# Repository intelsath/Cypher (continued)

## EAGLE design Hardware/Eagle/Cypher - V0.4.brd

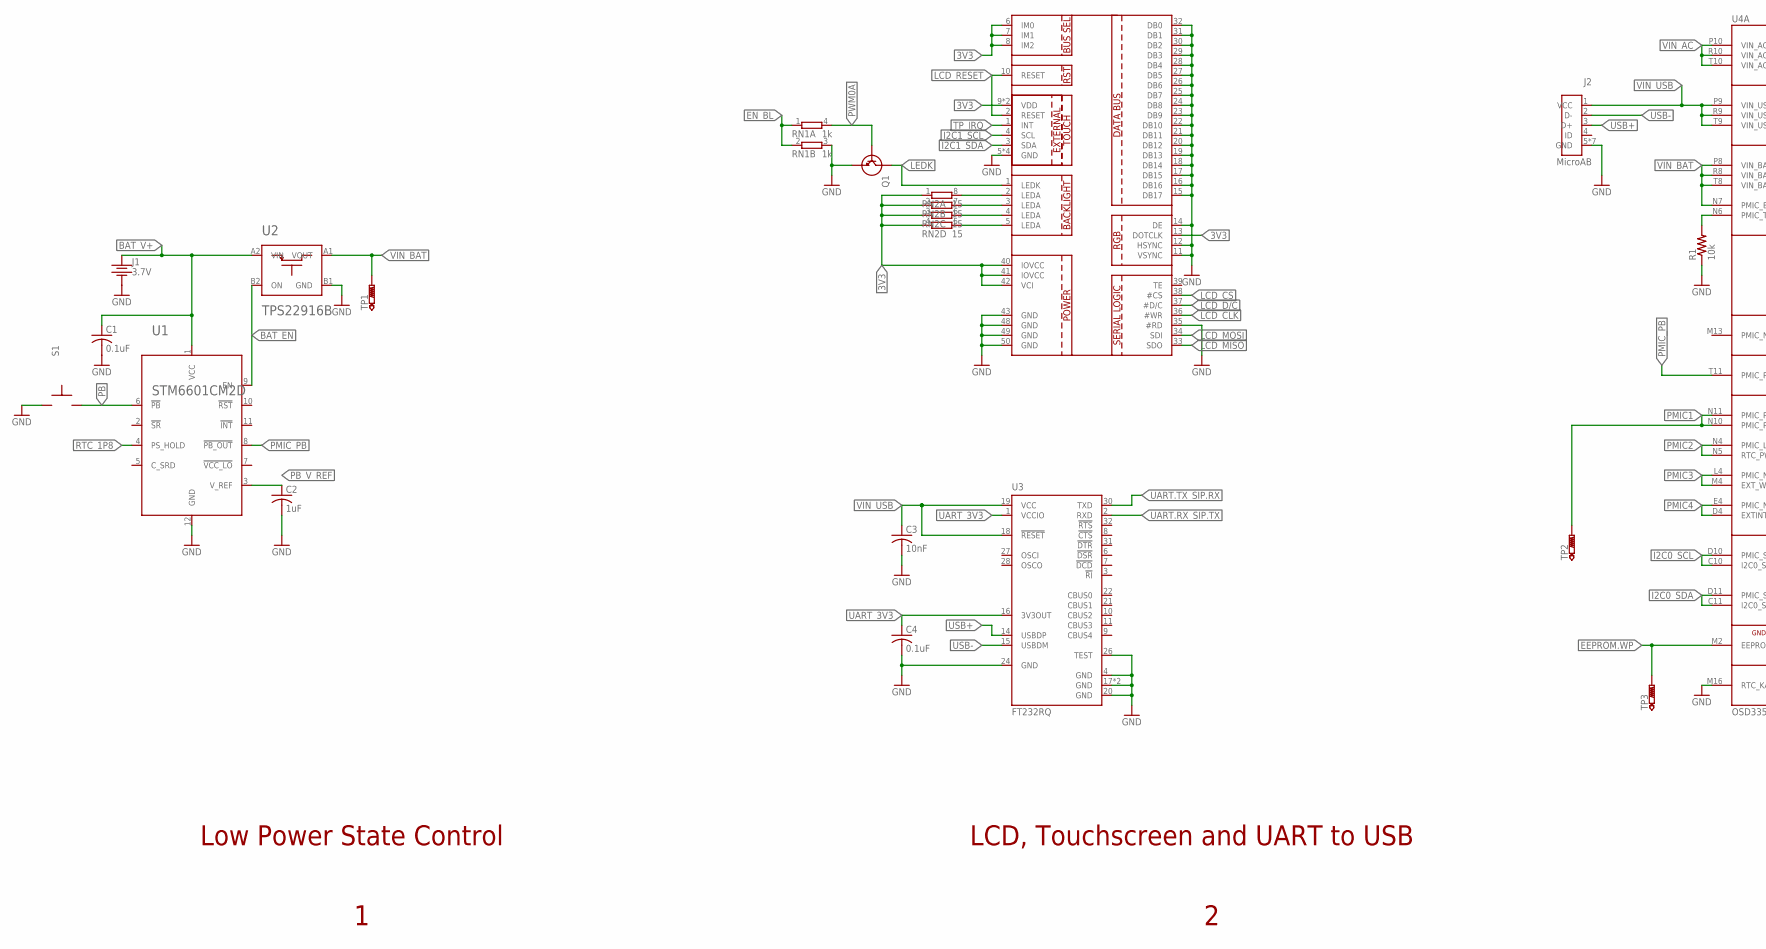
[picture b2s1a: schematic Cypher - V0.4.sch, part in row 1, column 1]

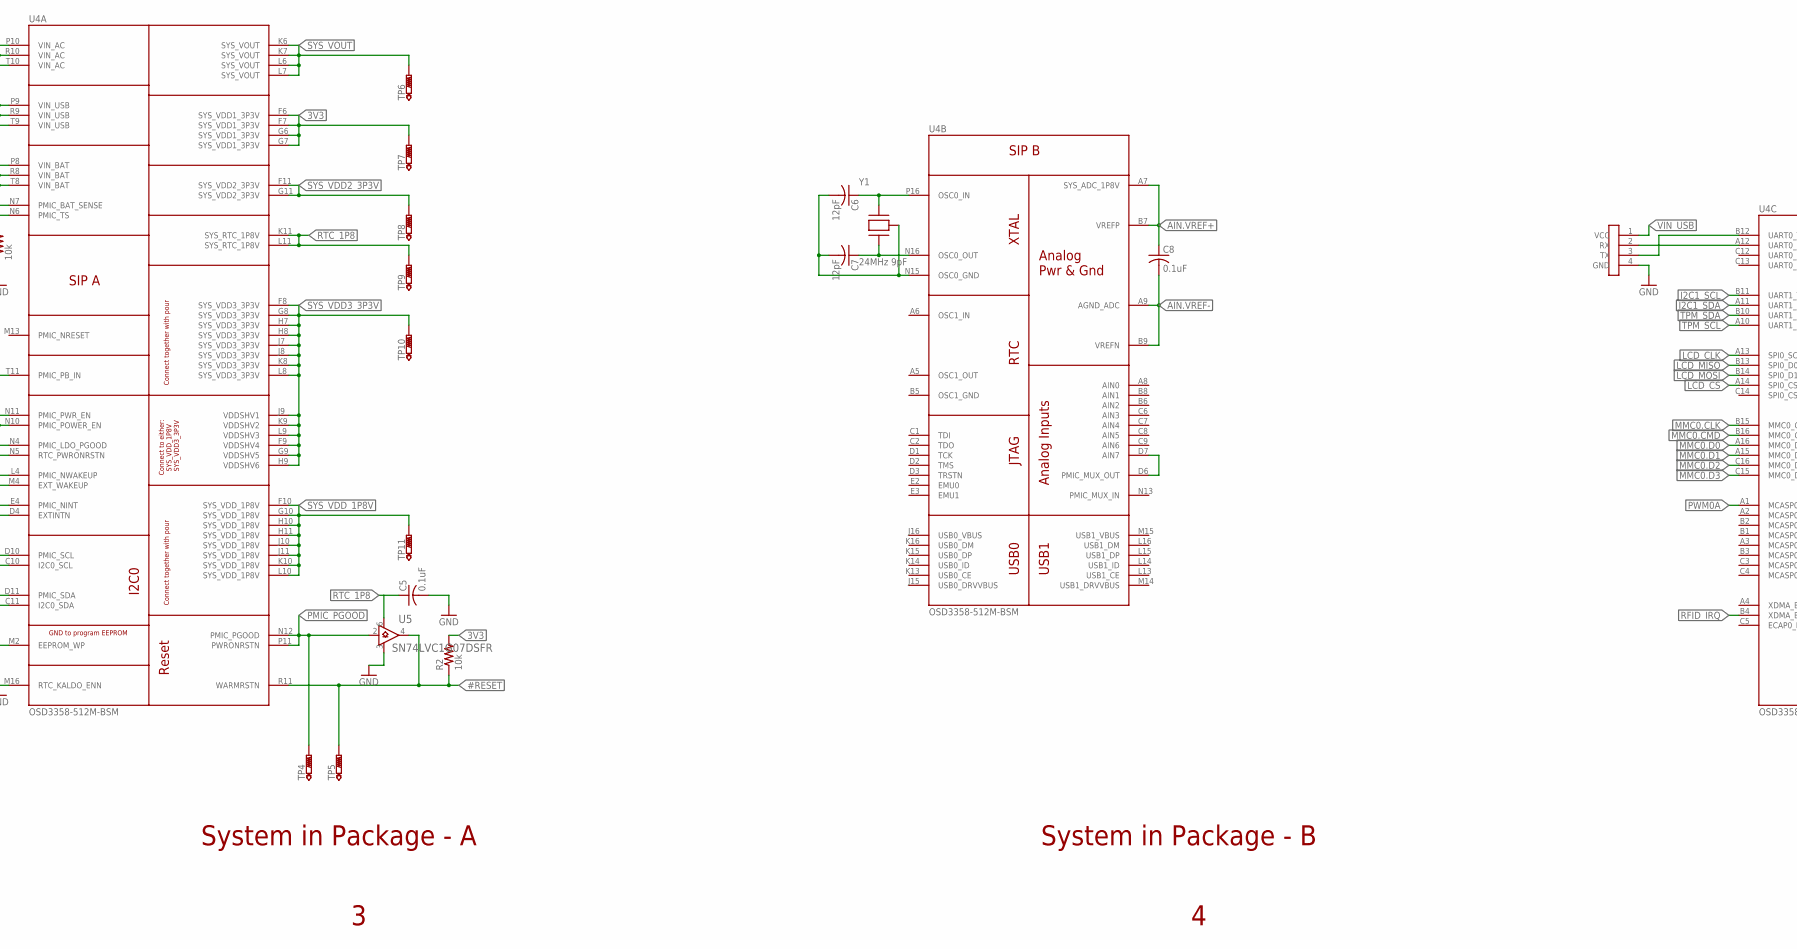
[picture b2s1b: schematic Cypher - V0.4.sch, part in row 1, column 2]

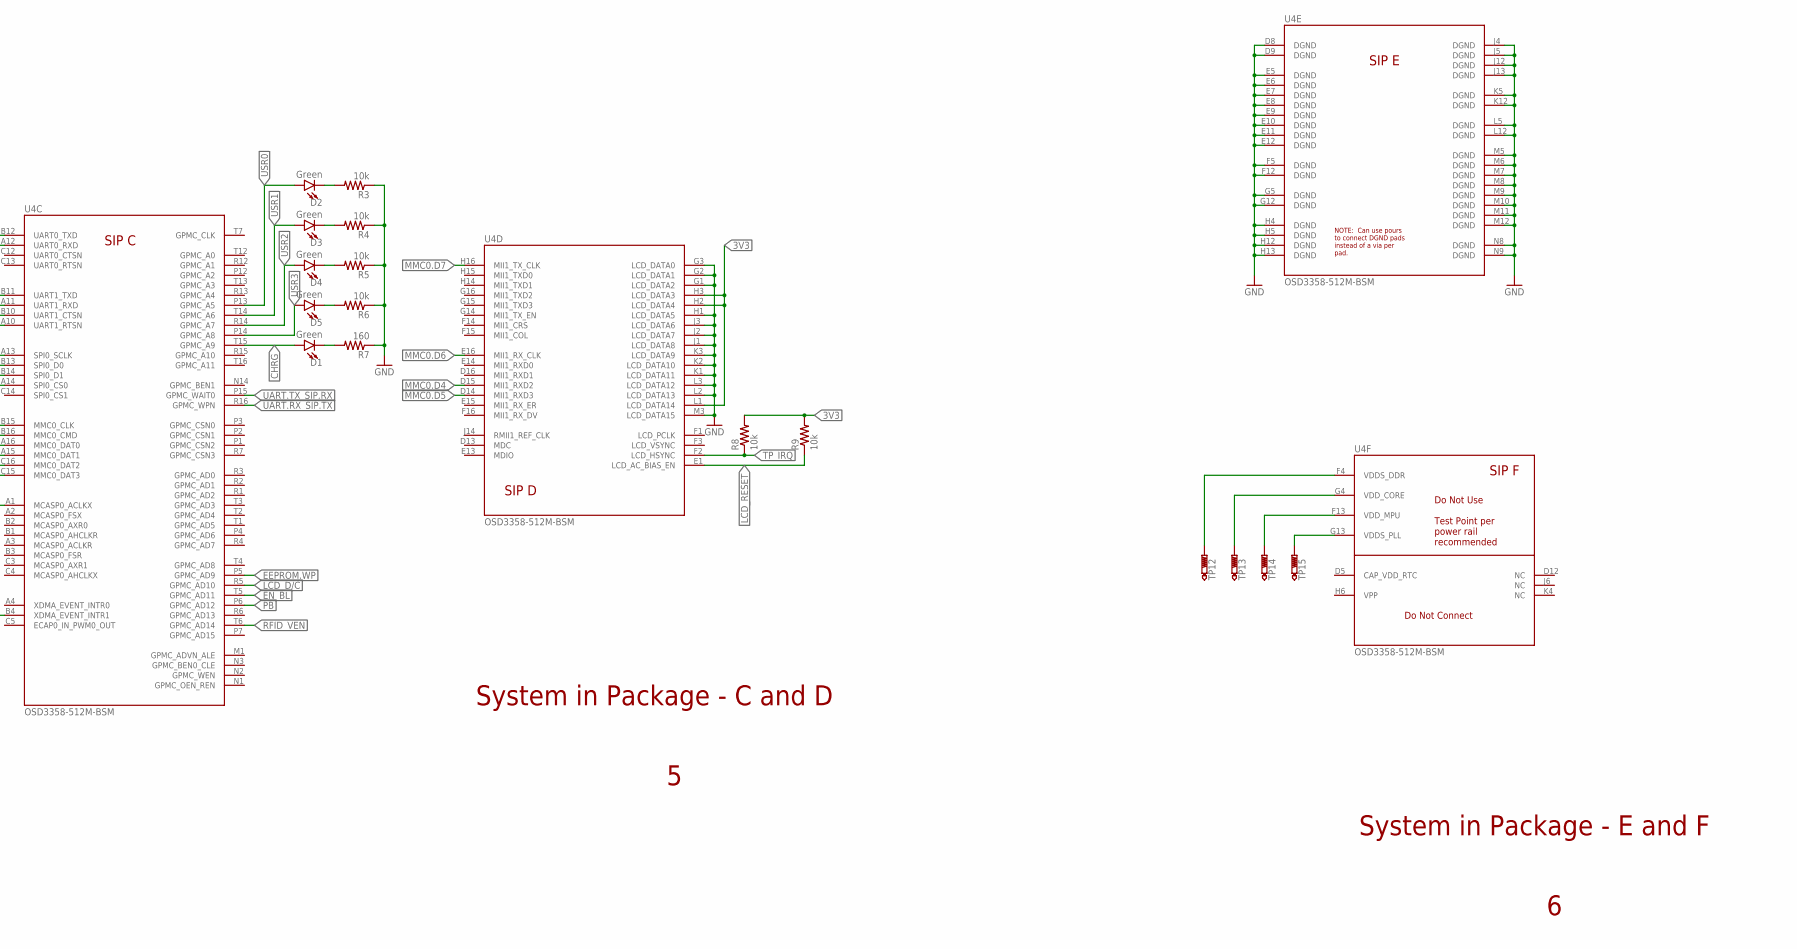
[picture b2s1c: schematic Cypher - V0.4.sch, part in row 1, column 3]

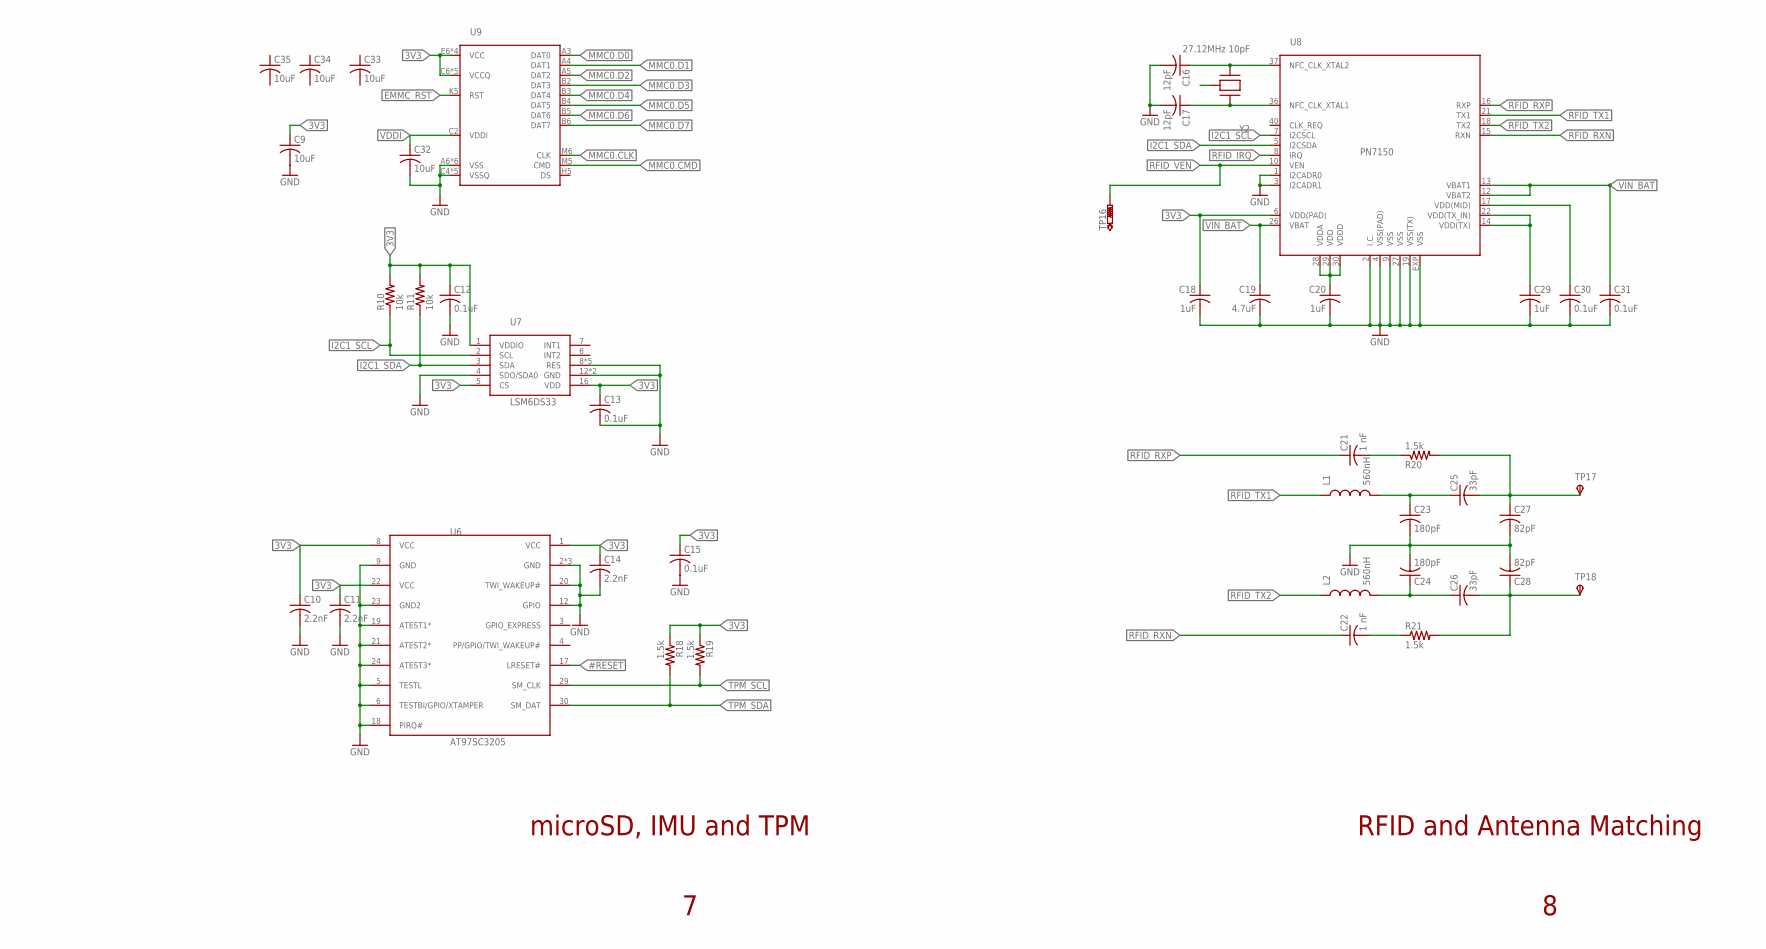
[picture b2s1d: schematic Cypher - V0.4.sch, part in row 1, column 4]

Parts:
C1, C4, C5, C8, C12, C13, C15, C30, C31: 0.1uF; C0402
C2, C18, C20, C29: 1uF; C0402
C3: 10nF; C0402
C6, C7, C16, C17: 12pF; C0402
C9, C32, C33, C34, C35: 10uF; C0402
C10, C11, C14: 2.2nF; C0402
C19: 4.7uF; C0402
C21, C22: 1 nF; C0603
C23, C24: 180pF; C0402
C25, C26: 33pF; C0402
C27, C28: 82pF; C0402
D1, D2, D3, D4, D5: Green; LED-0603
J1: 3.7V; SH_CONNECTOR
J2: MicroAB; MICRO-USB-AB-SMD
J3: UARTPINSSH; SM04B-SRSS-TB
L1, L2: 560nH; C0402
Q1: MMBT2222ASOT23; SOT-23-3
R1, R2, R3, R4, R5, R6, R8, R9, R10, R11: 10k; R0402
R7: 160; R0402
R18, R19, R20, R21: 1.5k; R0402
RN1: 1k; EXBV4V
RN2: 15; EXBN8V
S1: PUSHBUTTON1.2; EVQ-PUK
TP1, TP2, TP3, TP4, TP5, TP6, TP7, TP8, TP9, TP10, TP11, TP12, TP13, TP14, TP15, TP16: PTR1B1,27; B1,27
TP17, TP18: TPSB2,54; B2,54
U1: STM6601CM2D; TDFN12
U2: TPS22916B; WSON-4PIN
U3: FT232RQ; QFN32; MPN FT232RQ-REEL
U4: OSD3358-512M-BSM; OSD335X-BGA-256; MPN BB-POCKET
U5: SN74LVC1G07DSFR; SON35P100X100X40-6N
U6: AT97SC3205; QFN32-4MM
U7: LSM6DS33; LGA-16; MPN LSM6DS33TR
U8: PN7150; HVQFN40
U9: EMMC_EM-20; 153-LFBGA
XU1: CAPTOUCHSCREEN_6PINFPC10PIN; DF37NB-10DS-0.4V
XU2: ILI9388_50PIN_SOCKET; FPC/FFC_50PIN_0.5MMPITCH
Y1: 24MHz 9pF; 4-SMD
Y2: 27.12MHz 10pF; XRCGB

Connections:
3V3: C9.1, C10.1, C11.1, C12.1, C13.1, C14.1, C15.1, C18.1, R2.2, R8.2, R9.2, R10.2, R11.2, R18.1, R19.1, RN2.1, RN2.2 (1), RN2.3 (1), RN2.4 (1), TP7.TP, U4.F6 (SYS_VDD1_3P3V), U4.F7 (SYS_VDD1_3P3V), U4.G6 (SYS_VDD1_3P3V), U4.G7 (SYS_VDD1_3P3V), U4.H2 (LCD_DATA4), U4.H3 (LCD_DATA3), U4.L1 (LCD_DATA14), U6.1 (VCC), U6.8 (VCC), U6.22 (VCC), U7.1 (VDDIO), U7.5 (CS), U7.16 (VDD), U8.6 (VDD(PAD)), U9.C6 (VCCQ), U9.E6 (VCC), U9.F5 (VCC), U9.J10 (VCC), U9.K9 (VCC), U9.M4 (VCCQ), U9.N4 (VCCQ), U9.P3 (VCCQ), U9.P5 (VCCQ), XU1.9 (VDD), XU1.10 (VDD), XU2.6 (IM0), XU2.7 (IM1), XU2.8 (IM2), XU2.13 (DOTCLK), XU2.40 (IOVCC), XU2.41 (IOVCC), XU2.42 (VCI)
#RESET: R2.1, TP5.TP, U4.R11 (WARMRSTN), U5.4 (Y), U6.17 (LRESET#)
AIN.VREF+: C8.1, U4.A7 (SYS_ADC_1P8V), U4.B7 (VREFP)
AIN.VREF-: C8.2, U4.A9 (AGND_ADC), U4.B9 (VREFN)
ANT_1: C25.2, C27.1, R20.2, TP17.TP
ANT_2: C26.2, C28.1, R21.2, TP18.TP
BAT_EN: U1.9 (EN), U2.B2 (ON)
BAT_V+: C1.1, J1.2 (V+), U1.1 (VCC), U2.A2 (VIN)
CHRG: D1.A, U4.T15 (GPMC_A9)
D2_CAT: D2.C, R3.2
D2_CAT1: D1.C, R7.2
D3_CAT: D3.C, R4.2
D4_CAT: D4.C, R5.2
D5_CAT: D5.C, R6.2
EEPROM.WP: TP3.TP, U4.M2 (EEPROM_WP), U4.P5 (GPMC_AD9)
EMCF_ANTM1: C23.1, C25.1, L1.2
EMCF_ANTM2: C24.1, C26.1, L2.2
EMMC_RST: U9.K5 (RST)
EN_BL: RN1.1, RN1.2 (1), U4.T5 (GPMC_AD11)
GND: C1.2, C2.2, C3.2, C4.2, C5.2, C9.2, C10.2, C11.2, C12.2, C13.2, C14.2, C15.2, C16.2, C17.2, C18.2, C19.2, C20.2, C23.2, C24.2, C27.2, C28.2, C29.2, C30.2, C31.2, C32.2, J1.1 (V-), J2.5 (GND), J2.PAD1 (GND), J2.PAD2 (GND), J2.PAD3 (GND), J2.PAD4 (GND), J2.PAD5 (GND), J2.PAD6 (GND), J3.4 (GND), Q1.E, R1.1, R3.1, R4.1, R5.1, R6.1, R7.1, RN1.3 (2), S1.2, S1.4 (2), U1.12 (GND), U2.B1 (GND), U3.4 (GND), U3.17 (GND), U3.20 (GND), U3.24 (GND), U3.26 (TEST), U3.EXP (GND), U4.D8 (DGND), U4.D9 (DGND), U4.E5 (DGND), U4.E6 (DGND), U4.E7 (DGND), U4.E8 (DGND), U4.E9 (DGND), U4.E10 (DGND), U4.E11 (DGND), U4.E12 (DGND), U4.F5 (DGND), U4.F12 (DGND), U4.G1 (LCD_DATA2), U4.G2 (LCD_DATA1), U4.G3 (LCD_DATA0), U4.G5 (DGND), U4.G12 (DGND), U4.H1 (LCD_DATA5), U4.H4 (DGND), U4.H5 (DGND), U4.H12 (DGND), U4.H13 (DGND), U4.J1 (LCD_DATA8), U4.J2 (LCD_DATA7), U4.J3 (LCD_DATA6), U4.J4 (DGND), U4.J5 (DGND), U4.J12 (DGND), U4.J13 (DGND), U4.K1 (LCD_DATA11), U4.K2 (LCD_DATA10), U4.K3 (LCD_DATA9), U4.K5 (DGND), U4.K12 (DGND), U4.L2 (LCD_DATA13), U4.L3 (LCD_DATA12), U4.L5 (DGND), U4.L12 (DGND), U4.M3 (LCD_DATA15), U4.M5 (DGND), U4.M6 (DGND), U4.M7 (DGND), U4.M8 (DGND), U4.M9 (DGND), U4.M10 (DGND), U4.M11 (DGND), U4.M12 (DGND), U4.M16 (RTC_KALDO_ENN), U4.N8 (DGND), U4.N9 (DGND), U5.3 (GND), U6.2 (GND), U6.5 (TESTL), U6.6 (TESTBI/GPIO/XTAMPER), U6.9 (GND), U6.12 (GPIO), U6.18 (PIRQ#), U6.19 (ATEST1*), U6.20 (TWI_WAKEUP#), U6.21 (ATEST2*), U6.23 (GND2), U6.24 (ATEST3*), U6.32 (GND), U6.EXP (GND), U7.4 (SDO/SDA0), U7.8 (RES), U7.9 (RES), U7.10 (RES), U7.11 (RES), U7.12 (GND), U7.13 (GND), U7.15 (RES), U8.1 (I2CADR0), U8.2 (I.C.), U8.3 (I2CADR1), U8.4 (VSS(PAD)), U8.9 (VSS), U8.19 (VSS(TX)), U8.27 (VSS), U8.EXP (VSS), U9.A6 (VSS), U9.C4 (VSSQ), U9.E7 (VSS), U9.G5 (VSS), U9.H10 (VSS), U9.J5 (VSS), U9.K8 (VSS), U9.N2 (VSSQ), U9.N5 (VSSQ), U9.P4 (VSSQ), U9.P6 (VSSQ), XU1.5 (GND), XU1.6 (GND), XU1.7 (GND), XU1.8 (GND), XU2.11 (VSYNC), XU2.12 (HSYNC), XU2.14 (DE), XU2.15 (DB17), XU2.16 (DB16), XU2.17 (DB15), XU2.18 (DB14), XU2.19 (DB13), XU2.20 (DB12), XU2.21 (DB11), XU2.22 (DB10), XU2.23 (DB9), XU2.24 (DB8), XU2.25 (DB7), XU2.26 (DB6), XU2.27 (DB5), XU2.28 (DB4), XU2.29 (DB3), XU2.30 (DB2), XU2.31 (DB1), XU2.32 (DB0), XU2.35 (#RD), XU2.43 (GND), XU2.48 (GND), XU2.49 (GND), XU2.50 (GND)
I2C0_SCL: U4.C10 (I2C0_SCL), U4.D10 (PMIC_SCL)
I2C0_SDA: U4.C11 (I2C0_SDA), U4.D11 (PMIC_SDA)
I2C1_SCL: R10.1, U4.B11 (UART1_TXD), U7.2 (SCL), U8.7 (I2CSCL), XU1.4 (SCL)
I2C1_SDA: R11.1, U4.A11 (UART1_RXD), U7.3 (SDA), U8.5 (I2CSDA), XU1.3 (SDA)
LCD_CLK: U4.A13 (SPI0_SCLK), XU2.36 (#WR)
LCD_CS: U4.A14 (SPI0_CS0), XU2.38 (#CS)
LCD_D/C: U4.R5 (GPMC_AD10), XU2.37 (#D/C)
LCD_MISO: U4.B13 (SPI0_D0), XU2.33 (SDO)
LCD_MOSI: U4.B14 (SPI0_D1), XU2.34 (SDI)
LCD_RESET: R9.1, U4.E1 (LCD_AC_BIAS_EN), XU1.2 (RESET), XU2.10 (RESET)
LEDA@2: RN2.8 (2), XU2.2 (LEDA)
LEDA@3: RN2.7 (2), XU2.3 (LEDA)
LEDA@4: RN2.6 (2), XU2.4 (LEDA)
LEDA@5: RN2.5 (2), XU2.5 (LEDA)
LEDK: Q1.C, XU2.1 (LEDK)
MMC0.CLK: U4.B15 (MMC0_CLK), U9.M6 (CLK)
MMC0.CMD: U4.B16 (MMC0_CMD), U9.M5 (CMD)
MMC0.D0: U4.A16 (MMC0_DAT0), U9.A3 (DAT0)
MMC0.D1: U4.A15 (MMC0_DAT1), U9.A4 (DAT1)
MMC0.D2: U4.C16 (MMC0_DAT2), U9.A5 (DAT2)
MMC0.D3: U4.C15 (MMC0_DAT3), U9.B2 (DAT3)
MMC0.D4: U4.D15 (MII1_RXD2), U9.B3 (DAT4)
MMC0.D5: U4.D14 (MII1_RXD3), U9.B4 (DAT5)
MMC0.D6: U4.E16 (MII1_RX_CLK), U9.B5 (DAT6)
MMC0.D7: U4.H16 (MII1_TX_CLK), U9.B6 (DAT7)
NC: Y2.2 (GND), Y2.4 (GND)
OSC_GND: C6.2, C7.2, U4.N15 (OSC0_GND), Y1.2 (GND), Y1.4 (GND)
PB: S1.1, S1.3 (1), U1.6 (!PB), U4.P6 (GPMC_AD12)
PB_V_REF: C2.1, U1.3 (V_REF)
PMIC1: TP2.TP, U4.N10 (PMIC_POWER_EN), U4.N11 (PMIC_PWR_EN)
PMIC2: U4.N4 (PMIC_LDO_PGOOD), U4.N5 (RTC_PWRONRSTN)
PMIC3: U4.L4 (PMIC_NWAKEUP), U4.M4 (EXT_WAKEUP)
PMIC4: U4.D4 (EXTINTN), U4.E4 (PMIC_NINT)
PMIC_MUX: U4.D6 (PMIC_MUX_OUT), U4.D7 (AIN7)
PMIC_PB: U1.8 (!PB_OUT), U4.T11 (PMIC_PB_IN)
PMIC_PGOOD: TP4.TP, U4.N12 (PMIC_PGOOD), U4.P11 (PWRONRSTN), U5.2 (A)
PMIC_TS: R1.2, U4.N6 (PMIC_TS)
PWM0A: Q1.B, RN1.4 (2), U4.A1 (MCASP0_ACLKX)
RFID_IRQ: U4.B4 (XDMA_EVENT_INTR1), U8.8 (IRQ)
RFID_MISC_1: C21.2, R20.1
RFID_MISC_2: C22.2, R21.1
RFID_OSC_IN: C17.1, U8.36 (NFC_CLK_XTAL1), Y2.1 (OSC_IN)
RFID_OSC_OUT: C16.1, U8.37 (NFC_CLK_XTAL2), Y2.3 (OSC_OUT)
RFID_RXN: C22.1, U8.15 (RXN)
RFID_RXP: C21.1, U8.16 (RXP)
RFID_TX1: L1.1, U8.21 (TX1)
RFID_TX2: L2.1, U8.18 (TX2)
RFID_VEN: TP16.TP, U4.T6 (GPMC_AD14), U8.10 (VEN)
RTC_1P8: C5.1, TP9.TP, U1.4 (PS_HOLD), U4.K11 (SYS_RTC_1P8V), U4.L11 (SYS_RTC_1P8V), U5.6 (VCC)
SIP_OSC_IN: C6.1, U4.P16 (OSC0_IN), Y1.1 (OSC_IN)
SIP_OSC_OUT: C7.1, U4.N16 (OSC0_OUT), Y1.3 (OSC_OUT)
SYS_VDD2_3P3V: TP8.TP, U4.F11 (SYS_VDD2_3P3V), U4.G11 (SYS_VDD2_3P3V)
SYS_VDD3_3P3V: TP10.TP, U4.F8 (SYS_VDD3_3P3V), U4.F9 (VDDSHV4), U4.G8 (SYS_VDD3_3P3V), U4.G9 (VDDSHV5), U4.H7 (SYS_VDD3_3P3V), U4.H8 (SYS_VDD3_3P3V), U4.H9 (VDDSHV6), U4.J7 (SYS_VDD3_3P3V), U4.J8 (SYS_VDD3_3P3V), U4.J9 (VDDSHV1), U4.K8 (SYS_VDD3_3P3V), U4.K9 (VDDSHV2), U4.L8 (SYS_VDD3_3P3V), U4.L9 (VDDSHV3)
SYS_VDD_1P8V: TP11.TP, U4.F10 (SYS_VDD_1P8V), U4.G10 (SYS_VDD_1P8V), U4.H10 (SYS_VDD_1P8V), U4.H11 (SYS_VDD_1P8V), U4.J10 (SYS_VDD_1P8V), U4.J11 (SYS_VDD_1P8V), U4.K10 (SYS_VDD_1P8V), U4.L10 (SYS_VDD_1P8V)
SYS_VOUT: TP6.TP, U4.K6 (SYS_VOUT), U4.K7 (SYS_VOUT), U4.L6 (SYS_VOUT), U4.L7 (SYS_VOUT)
TPM_SCL: R19.2, U4.A10 (UART1_RTSN), U6.29 (SM_CLK)
TPM_SDA: R18.2, U4.B10 (UART1_CTSN), U6.30 (SM_DAT)
TP_IRQ: R8.1, U4.F2 (LCD_HSYNC), XU1.1 (INT)
UART0_RX: J3.2 (RX), U4.A12 (UART0_RXD)
UART0_TX: J3.3 (TX), U4.B12 (UART0_TXD)
UART.RX_SIP.TX: U3.2 (RXD), U4.R16 (GPMC_WPN)
UART.TX_SIP.RX: U3.30 (TXD), U4.P15 (GPMC_WAIT0)
UART_3V3: C4.1, U3.1 (VCCIO), U3.16 (3V3OUT)
USB+: J2.3 (D+), U3.14 (USBDP)
USB-: J2.2 (D-), U3.15 (USBDM)
USR0: D2.A, U4.P13 (GPMC_A5)
USR1: D3.A, U4.T14 (GPMC_A6)
USR2: D4.A, U4.R14 (GPMC_A7)
USR3: D5.A, U4.P14 (GPMC_A8)
VDD: C20.1, U8.28 (VDDA), U8.29 (VDD), U8.30 (VDDD)
VDD(MID): C30.1, U8.17 (VDD(MID))
VDD(TX): C29.1, U8.14 (VDD(TX)), U8.22 (VDD(TX_IN))
VDDI: C32.1, U9.C2 (VDDI)
VDDS_DDR: TP12.TP, U4.F4 (VDDS_DDR)
VDDS_PLL: TP15.TP, U4.G13 (VDDS_PLL)
VDD_CORE: TP13.TP, U4.G4 (VDD_CORE)
VDD_MPU: TP14.TP, U4.F13 (VDD_MPU)
VIN_AC: U4.P10 (VIN_AC), U4.R10 (VIN_AC), U4.T10 (VIN_AC)
VIN_BAT: C19.1, C31.1, TP1.TP, U2.A1 (VOUT), U4.N7 (PMIC_BAT_SENSE), U4.P8 (VIN_BAT), U4.R8 (VIN_BAT), U4.T8 (VIN_BAT), U8.12 (VBAT2), U8.13 (VBAT1), U8.26 (VBAT)
VIN_USB: C3.1, J2.1 (VCC), J3.1 (VCC), U3.18 (!RESET), U3.19 (VCC), U4.P9 (VIN_USB), U4.R9 (VIN_USB), U4.T9 (VIN_USB)

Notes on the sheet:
LCD, Touchscreen and UART to USB
System in Package - A
System in Package - B
System in Package - C and D
System in Package - E and F
microSD, IMU and TPM
RFID and Antenna Matching
Low Power State Control

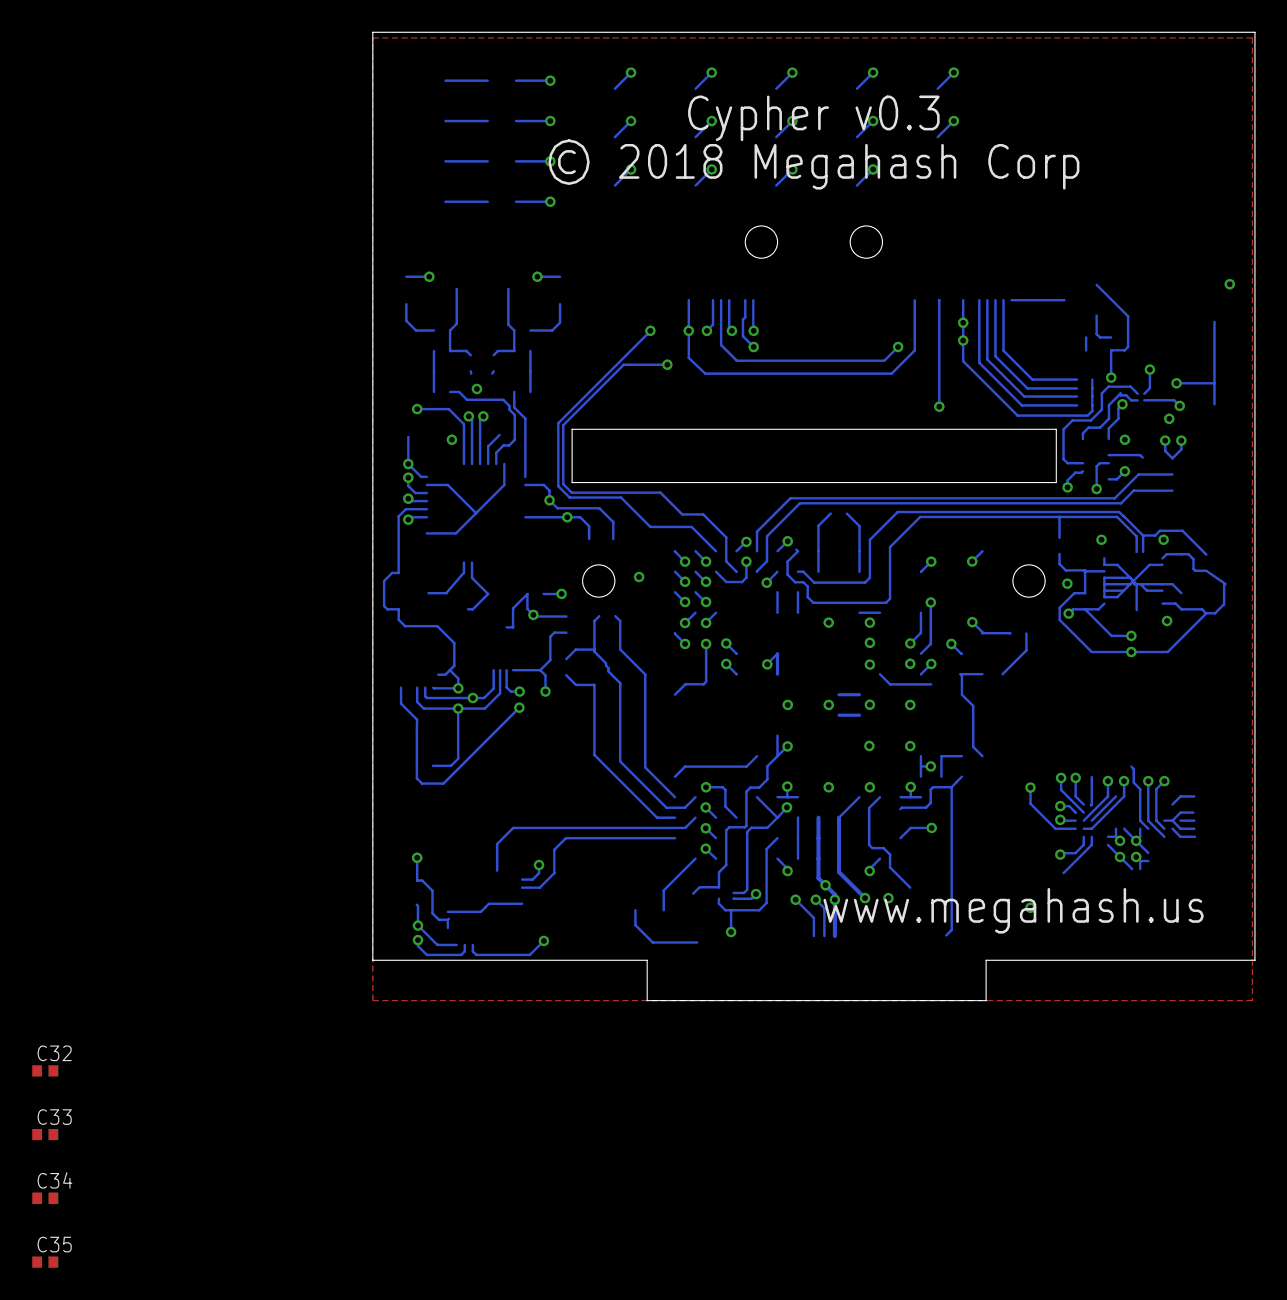
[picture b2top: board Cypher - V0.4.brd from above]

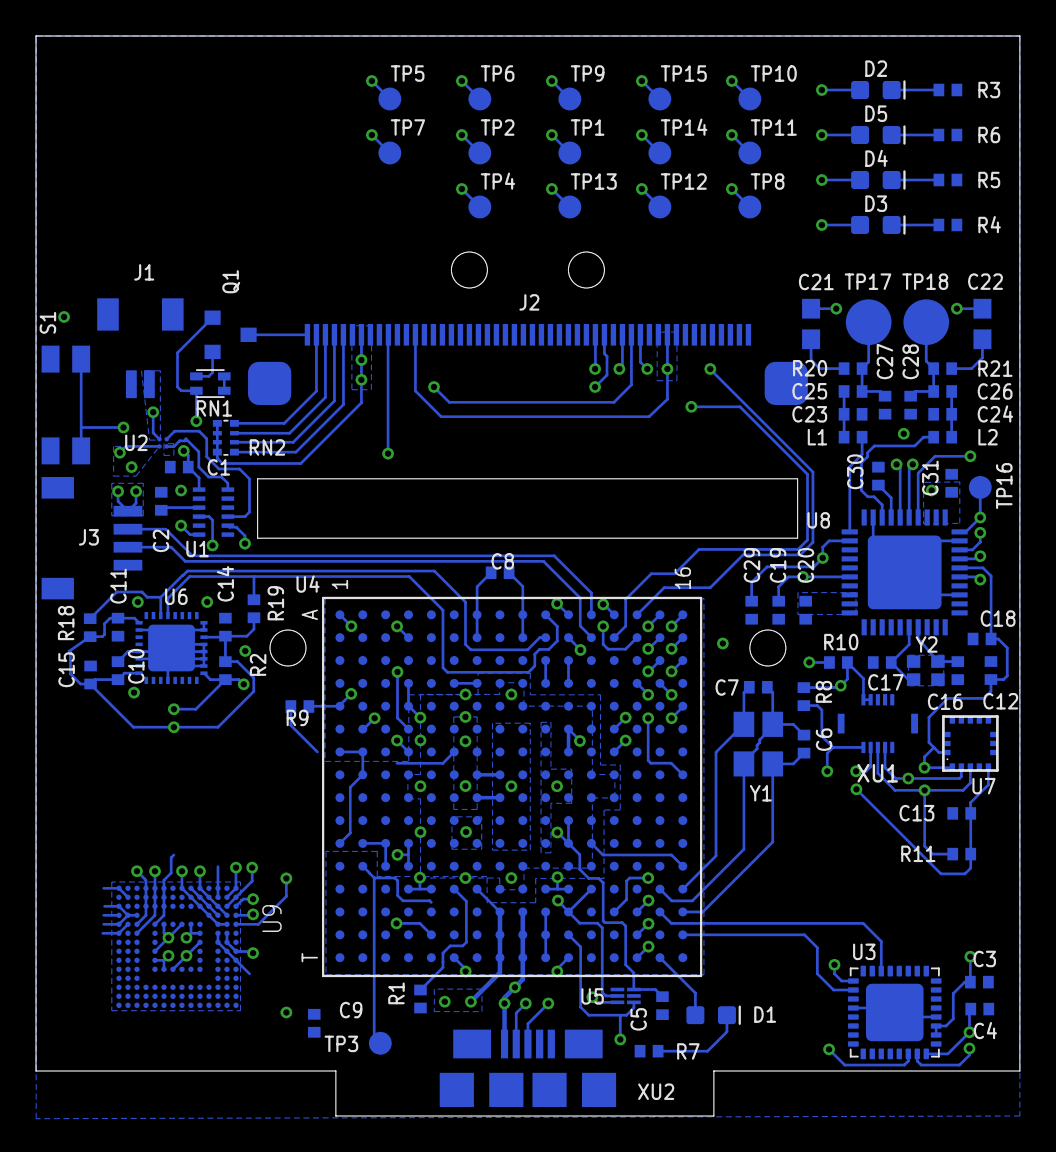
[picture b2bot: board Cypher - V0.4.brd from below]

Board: 4 copper layers, 54.7 x 60.0 mm, 95 parts (91 on the bottom side), 99 nets.

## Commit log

2020-03-15 All code and schematics
2020-03-15 Embedded Code
2020-03-15 Bump node.extend from 2.0.0 to 2.0.2 in /hashbank/cryptolibs
    Bumps [node.extend](https://github.com/dreamerslab/node.extend) from 2.0.0 to 2.0.2.
    - [Release notes](https://github.com/dreamerslab/node.extend/releases)
    - [Changelog](https://github.com/dreamerslab/node.extend/blob/master/History.md)
    - [Commits](https://github.com/dreamerslab/node.extend/compare/v2.0.0...v2.0.2)
2020-03-15 Bump set-value from 3.0.0 to 3.0.1 in /hashbank/cryptolibs
    Bumps [set-value](https://github.com/jonschlinkert/set-value) from 3.0.0 to 3.0.1.
    - [Release notes](https://github.com/jonschlinkert/set-value/releases)
    - [Commits](https://github.com/jonschlinkert/set-value/compare/3.0.0...3.0.1)
2020-03-15 Hashbank Desktop App
    Electron
2020-03-15 Bump bootstrap from 4.1.3 to 4.3.1 in /hashbank_client_app
    Bumps [bootstrap](https://github.com/twbs/bootstrap) from 4.1.3 to 4.3.1.
    - [Release notes](https://github.com/twbs/bootstrap/releases)
    - [Commits](https://github.com/twbs/bootstrap/compare/v4.1.3...v4.3.1)
2020-03-15 Bump lodash from 4.17.11 to 4.17.15 in /hashbank_client_app
    Bumps [lodash](https://github.com/lodash/lodash) from 4.17.11 to 4.17.15.
    - [Release notes](https://github.com/lodash/lodash/releases)
    - [Commits](https://github.com/lodash/lodash/compare/4.17.11...4.17.15)
2020-03-15 Bump jquery from 3.3.1 to 3.4.0 in /hashbank_client_app
    Bumps [jquery](https://github.com/jquery/jquery) from 3.3.1 to 3.4.0.
    - [Release notes](https://github.com/jquery/jquery/releases)
    - [Commits](https://github.com/jquery/jquery/compare/3.3.1...3.4.0)
2020-03-15 Bump fstream from 1.0.11 to 1.0.12 in /hashbank_client_app
    Bumps [fstream](https://github.com/npm/fstream) from 1.0.11 to 1.0.12.
    - [Release notes](https://github.com/npm/fstream/releases)
    - [Commits](https://github.com/npm/fstream/compare/v1.0.11...v1.0.12)
2020-03-15 Bump set-value from 3.0.0 to 3.0.1 in /hashbank_client_app
    Bumps [set-value](https://github.com/jonschlinkert/set-value) from 3.0.0 to 3.0.1.
    - [Release notes](https://github.com/jonschlinkert/set-value/releases)
    - [Commits](https://github.com/jonschlinkert/set-value/compare/3.0.0...3.0.1)
2020-04-30 Bump jquery from 3.3.1 to 3.5.0 in /hashbank_client_app
    Bumps [jquery](https://github.com/jquery/jquery) from 3.3.1 to 3.5.0.
    - [Release notes](https://github.com/jquery/jquery/releases)
    - [Commits](https://github.com/jquery/jquery/compare/3.3.1...3.5.0)
2020-07-07 Bump electron from 1.8.8 to 7.2.4 in /hashbank_client_app
    Bumps [electron](https://github.com/electron/electron) from 1.8.8 to 7.2.4.
    - [Release notes](https://github.com/electron/electron/releases)
    - [Changelog](https://github.com/electron/electron/blob/master/docs/breaking-changes.md)
    - [Commits](https://github.com/electron/electron/compare/v1.8.8...v7.2.4)
2020-07-19 Bump lodash from 4.17.11 to 4.17.19 in /hashbank_client_app
    Bumps [lodash](https://github.com/lodash/lodash) from 4.17.11 to 4.17.19.
    - [Release notes](https://github.com/lodash/lodash/releases)
    - [Commits](https://github.com/lodash/lodash/compare/4.17.11...4.17.19)
2020-09-04 Bump decompress from 4.2.0 to 4.2.1 in /hashbank_client_app
    Bumps [decompress](https://github.com/kevva/decompress) from 4.2.0 to 4.2.1.
    - [Release notes](https://github.com/kevva/decompress/releases)
    - [Commits](https://github.com/kevva/decompress/compare/v4.2.0...v4.2.1)
2020-12-12 Bump ini from 1.3.5 to 1.3.8 in /hashbank_client_app
    Bumps [ini](https://github.com/isaacs/ini) from 1.3.5 to 1.3.8.
    - [Release notes](https://github.com/isaacs/ini/releases)
    - [Commits](https://github.com/isaacs/ini/compare/v1.3.5...v1.3.8)
2020-12-12 Bump ini from 1.3.5 to 1.3.8 in /hashbank/cryptolibs
    Bumps [ini](https://github.com/isaacs/ini) from 1.3.5 to 1.3.8.
    - [Release notes](https://github.com/isaacs/ini/releases)
    - [Commits](https://github.com/isaacs/ini/compare/v1.3.5...v1.3.8)
2021-01-28 Bump electron from 1.8.8 to 9.4.0 in /hashbank_client_app
    Bumps [electron](https://github.com/electron/electron) from 1.8.8 to 9.4.0.
    - [Release notes](https://github.com/electron/electron/releases)
    - [Changelog](https://github.com/electron/electron/blob/master/docs/breaking-changes.md)
    - [Commits](https://github.com/electron/electron/compare/v1.8.8...v9.4.0)
2021-03-31 Bump y18n from 3.2.1 to 3.2.2 in /hashbank_client_app
    Bumps [y18n](https://github.com/yargs/y18n) from 3.2.1 to 3.2.2.
    - [Release notes](https://github.com/yargs/y18n/releases)
    - [Changelog](https://github.com/yargs/y18n/blob/master/CHANGELOG.md)
    - [Commits](https://github.com/yargs/y18n/commits)
2021-05-09 Bump url-parse from 1.4.3 to 1.5.1 in /hashbank/cryptolibs
    Bumps [url-parse](https://github.com/unshiftio/url-parse) from 1.4.3 to 1.5.1.
    - [Release notes](https://github.com/unshiftio/url-parse/releases)
    - [Commits](https://github.com/unshiftio/url-parse/compare/1.4.3...1.5.1)
2021-05-11 Bump lodash from 4.17.11 to 4.17.21 in /hashbank_client_app
    Bumps [lodash](https://github.com/lodash/lodash) from 4.17.11 to 4.17.21.
    - [Release notes](https://github.com/lodash/lodash/releases)
    - [Commits](https://github.com/lodash/lodash/compare/4.17.11...4.17.21)
2021-05-11 Bump hosted-git-info from 2.7.1 to 2.8.9 in /hashbank_client_app
    Bumps [hosted-git-info](https://github.com/npm/hosted-git-info) from 2.7.1 to 2.8.9.
    - [Release notes](https://github.com/npm/hosted-git-info/releases)
    - [Changelog](https://github.com/npm/hosted-git-info/blob/v2.8.9/CHANGELOG.md)
    - [Commits](https://github.com/npm/hosted-git-info/compare/v2.7.1...v2.8.9)
2021-05-12 Bump chart.js from 2.7.2 to 2.9.4 in /hashbank_client_app
    Bumps [chart.js](https://github.com/chartjs/Chart.js) from 2.7.2 to 2.9.4.
    - [Release notes](https://github.com/chartjs/Chart.js/releases)
    - [Commits](https://github.com/chartjs/Chart.js/compare/v2.7.2...v2.9.4)
2021-06-21 Bump set-getter from 0.1.0 to 0.1.1 in /hashbank_client_app
    Bumps [set-getter](https://github.com/doowb/set-getter) from 0.1.0 to 0.1.1.
    - [Release notes](https://github.com/doowb/set-getter/releases)
    - [Commits](https://github.com/doowb/set-getter/commits/0.1.1)
    ---
    updated-dependencies:
    - dependency-name: set-getter
2021-06-21 Bump set-getter from 0.1.0 to 0.1.1 in /hashbank/cryptolibs
    Bumps [set-getter](https://github.com/doowb/set-getter) from 0.1.0 to 0.1.1.
    - [Release notes](https://github.com/doowb/set-getter/releases)
    - [Commits](https://github.com/doowb/set-getter/commits/0.1.1)
    ---
    updated-dependencies:
    - dependency-name: set-getter
